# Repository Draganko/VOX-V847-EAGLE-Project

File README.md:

# Vox-V847-Eagle-Project

This is a small repository for storing `EAGLE` files for the VOX V847 clone 
that I built.

You need the [EAGLE CAD](https://www.autodesk.com/products/eagle/overview) to 
open and view these files.

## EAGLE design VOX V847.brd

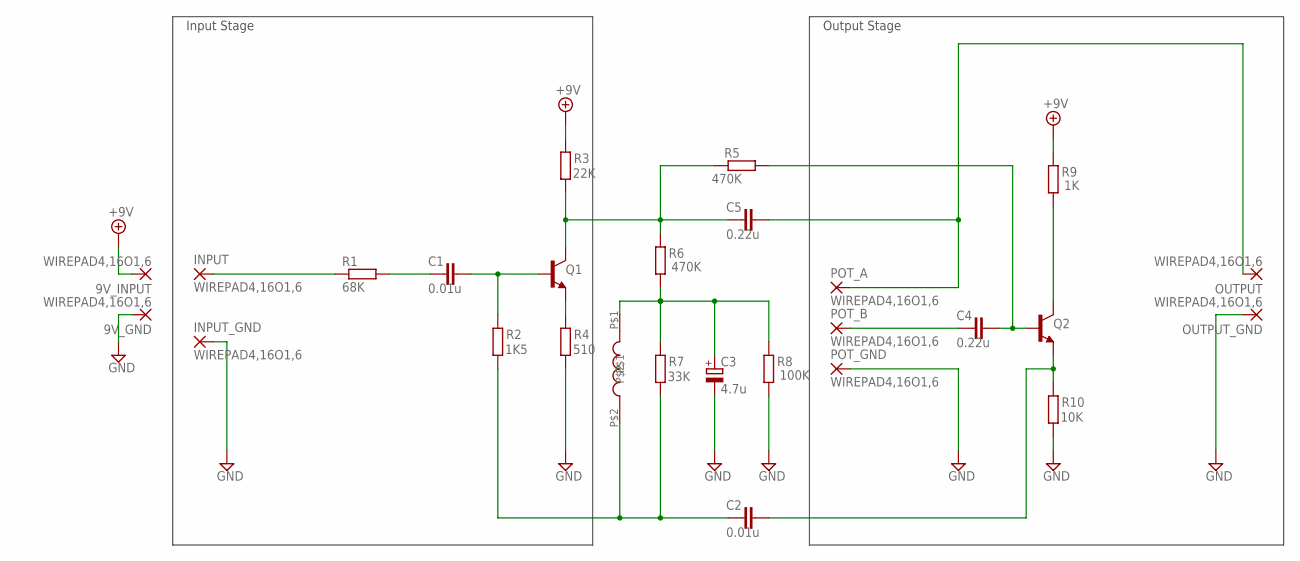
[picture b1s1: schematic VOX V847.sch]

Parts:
9V_GND, 9V_INPUT: WIREPAD4,16O1,6; 4,16O1,6
C1, C2: 0.01u; C050-024X044
C3: 4.7u; E5-5
C4: 0.22u; C075-042X103
C5: 0.22u; C050-024X044
INPUT: WIREPAD4,16O1,6; 4,16O1,6
INPUT_GND: WIREPAD4,16O1,6; 4,16O1,6
OUTPUT: WIREPAD4,16O1,6; 4,16O1,6
OUTPUT_GND: WIREPAD4,16O1,6; 4,16O1,6
POT_A: WIREPAD4,16O1,6; 4,16O1,6
POT_B: WIREPAD4,16O1,6; 4,16O1,6
POT_GND: WIREPAD4,16O1,6; 4,16O1,6
Q1, Q2: MPSA18-NPN-TO92-EBC; TO92-EBC
R1: 68K; 0207/7
R2: 1K5; 0207/12
R3: 22K; 0207/7
R4: 510; 0207/10
R5, R6: 470K; 0207/7
R7: 33K; 0207/7
R8: 100K; 0207/7
R9: 1K; 0207/12
R10: 10K; 0207/7
U$1: FL01Y

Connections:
+9V: 9V_INPUT.1, R3.2, R9.2
GND: 9V_GND.1, C3.-, INPUT_GND.1, OUTPUT_GND.1, POT_GND.1, R4.1, R8.1, R10.1
unnamed: INPUT.1, R1.1
unnamed: C1.2, Q1.B, R2.2
unnamed: C1.1, R1.2
unnamed: C2.2, Q2.E, R10.2
unnamed: Q1.E, R4.2
unnamed: C5.1, Q1.C, R3.1, R5.2, R6.2
unnamed: C3.+, R6.1, R7.2, R8.2, U$1.P$1
unnamed: C2.1, R2.1, R7.1, U$1.P$2
unnamed: C4.2, Q2.B, R5.1
unnamed: C4.1, POT_B.1
unnamed: C5.2, OUTPUT.1, POT_A.1
unnamed: Q2.C, R9.1

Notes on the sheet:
Input Stage
Output Stage

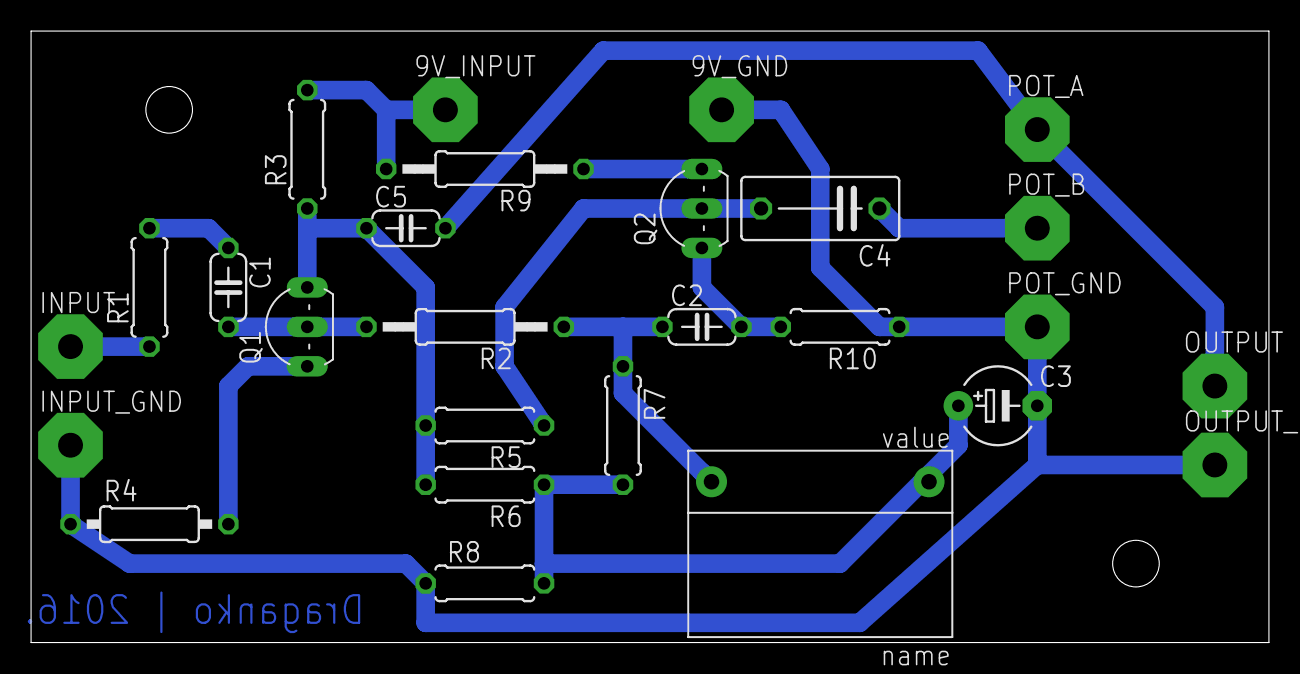
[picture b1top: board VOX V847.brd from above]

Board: 2 copper layers, 79.7 x 39.4 mm, 27 parts (0 on the bottom side), 14 nets.

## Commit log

2016-03-14 First Commit
    The project seems to be pretty much done, I'll work on some improvements
    to maybe make it a bit neater, but all in all, this is done.
2018-10-05 Added a README file
2018-10-05 Added a license
2018-10-05 Fixed image link in README

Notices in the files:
README.md:
CC BY-NC-SA 4.0
